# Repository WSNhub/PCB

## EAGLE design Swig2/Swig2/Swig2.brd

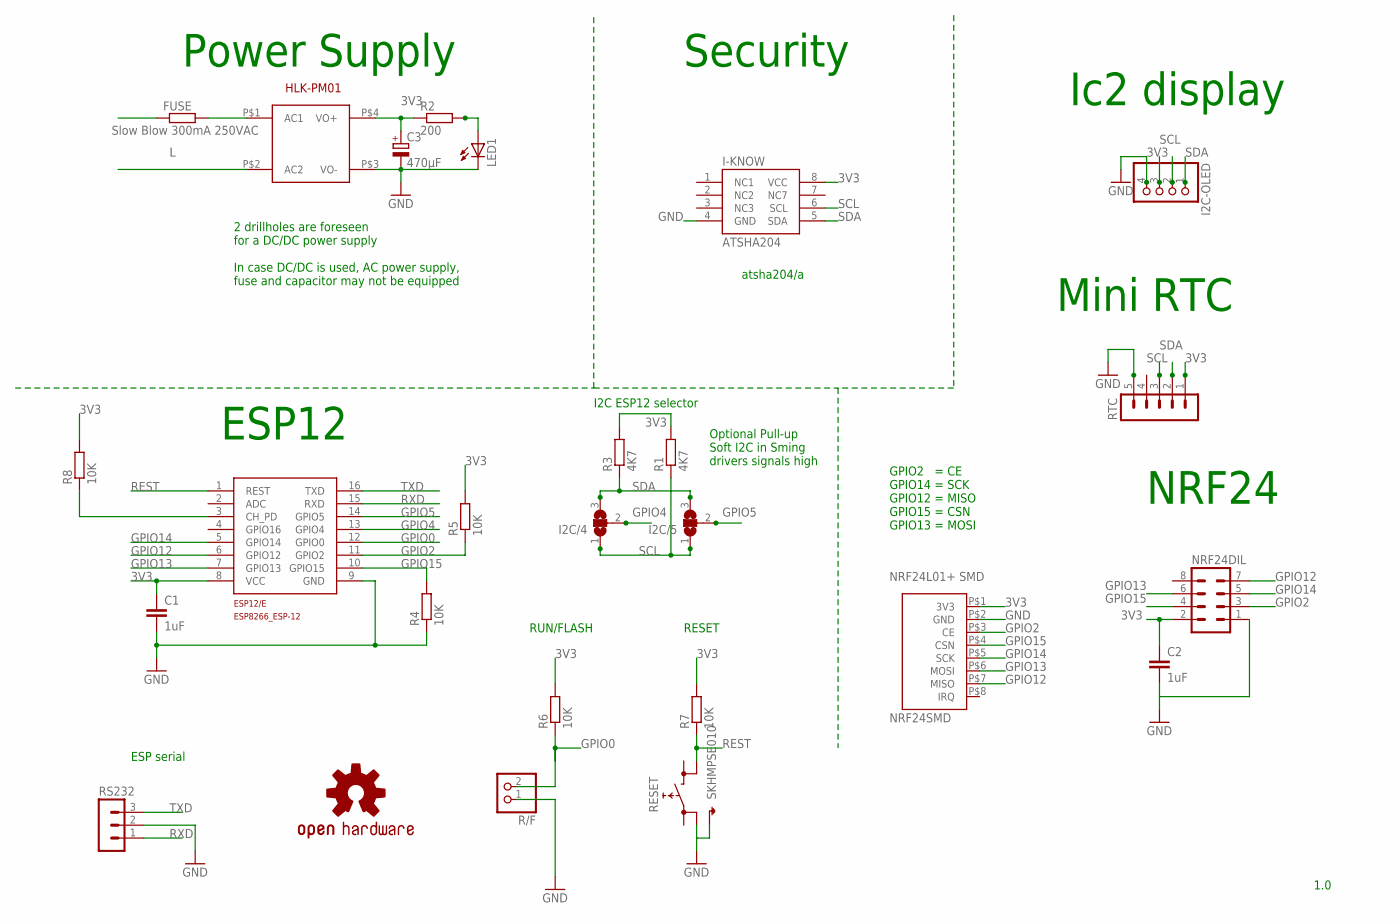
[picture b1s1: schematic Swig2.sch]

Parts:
C1, C2: 1uF; C0805
C3: 470µF; E5-8,5
ESP12/E: ESP8266-12GPIO04/05_CORRECTED; ESP8266-ESP12
FUSE: Slow Blow 300mA 250VAC; 0411V
HLK-PM01: HLK-PM01
I2C-OLED: PINHD-1X4; 1X04
I2C/4, I2C/5: SJ2W; SJ_2
I-KNOW: ATSHA204; SOIC8
LED1: LED5MM
LOGO2: OSHW-LOGOS; OSHW-LOGO-S
NRF24DIL: MA04-2
NRF24SMD: NRF24L01+SMD
R1, R3: 4K7; R0805
R2: 200; R0805
R4, R5, R6, R7, R8: 10K; R0805
R/F: PINHD-1X2; 1X02
RESET: SKHMPSE010; SKHMPXE010
RS232: MA03-1
RTC: MA05-1

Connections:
3V3: C1.1, C2.1, C3.+, ESP12/E.8 (VCC), HLK-PM01.P$4 (VO+), I2C-OLED.3, I-KNOW.8 (VCC), NRF24DIL.2, NRF24SMD.P$1 (3V3), R1.2, R2.1, R3.2, R5.2, R6.2, R7.2, R8.2, RTC.1
GND: C1.2, C2.2, C3.-, ESP12/E.9 (GND), HLK-PM01.P$3 (VO-), I2C-OLED.4, I-KNOW.4 (GND), LED1.K (C), NRF24DIL.1, NRF24SMD.P$2 (GND), R4.1, R/F.1, RESET.2 (1.2), RESET.5 (SH), RS232.2, RTC.5
GPIO0: ESP12/E.12 (GPIO0), R6.1, R/F.2
GPIO2: ESP12/E.11 (GPIO2), NRF24DIL.3, NRF24SMD.P$3 (CE), R5.1
GPIO4: ESP12/E.13 (GPIO4), I2C/4.2
GPIO5: ESP12/E.14 (GPIO5), I2C/5.2
GPIO12: ESP12/E.6 (GPIO12), NRF24DIL.7, NRF24SMD.P$7 (MISO)
GPIO13: ESP12/E.7 (GPIO13), NRF24DIL.6, NRF24SMD.P$6 (MOSI)
GPIO14: ESP12/E.5 (GPIO14), NRF24DIL.5, NRF24SMD.P$5 (SCK)
GPIO15: ESP12/E.10 (GPIO15), NRF24DIL.4, NRF24SMD.P$4 (CSN), R4.2
L: HLK-PM01.P$2 (AC2)
unnamed: FUSE.2, HLK-PM01.P$1 (AC1)
unnamed: ESP12/E.3 (CH_PD), R8.1
unnamed: LED1.A, R2.2
REST: ESP12/E.1 (REST), R7.1, RESET.4 (2.2)
RXD: ESP12/E.15 (RXD), RS232.1
SCL: I2C-OLED.2, I2C/4.1, I2C/5.1, I-KNOW.6 (SCL), R1.1, RTC.3
SDA: I2C-OLED.1, I2C/4.3, I2C/5.3, I-KNOW.5 (SDA), R3.1, RTC.2
TXD: ESP12/E.16 (TXD), RS232.3

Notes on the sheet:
ESP serial
RUN/FLASH
RESET
NRF24
1.0
I2C ESP12 selector
atsha204/a
Mini RTC
Power Supply
Security
ESP12
Optional Pull-up Soft I2C in Sming drivers signals high
2 drillholes are foreseen for a DC/DC power supply In case DC/DC is used, AC power supply, fuse and capacitor may not be equipped
Ic2 display
GPIO2 = CE GPIO14 = SCK GPIO12 = MISO GPIO15 = CSN GPIO13 = MOSI

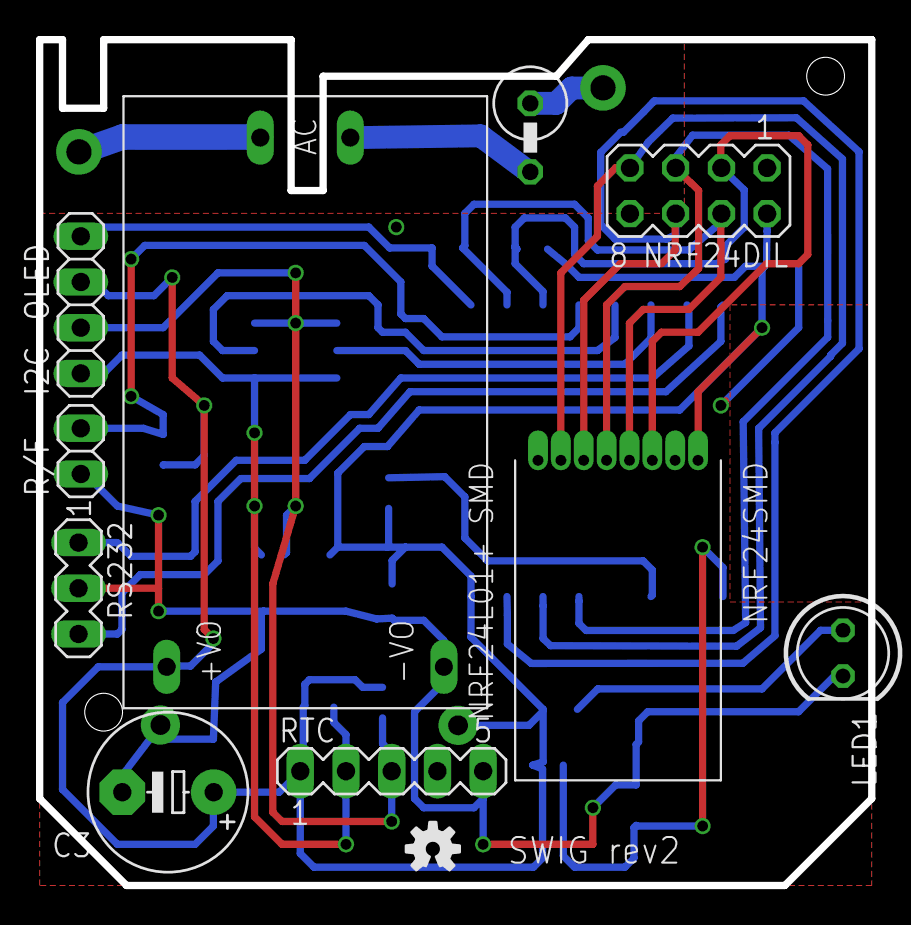
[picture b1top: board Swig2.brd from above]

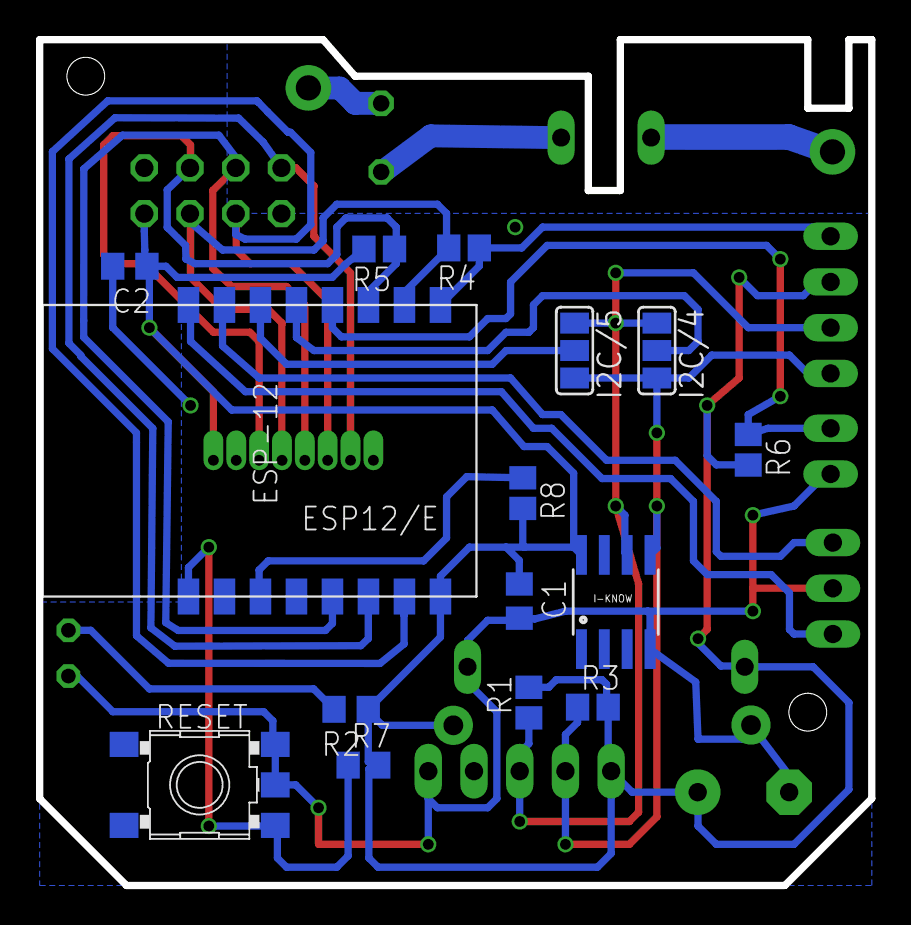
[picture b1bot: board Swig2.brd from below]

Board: 2 copper layers, 46.2 x 47.0 mm, 26 parts (15 on the bottom side), 18 nets.

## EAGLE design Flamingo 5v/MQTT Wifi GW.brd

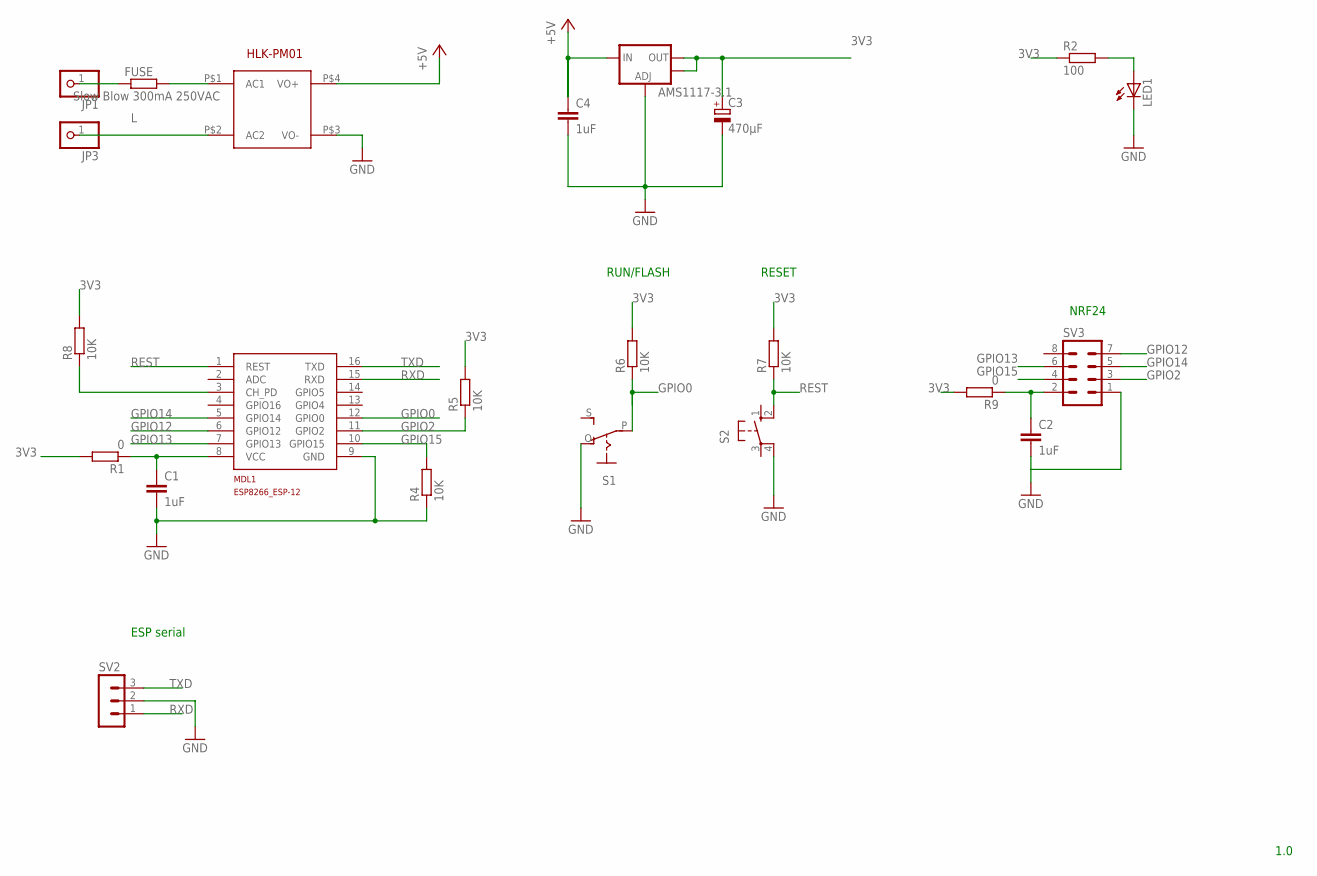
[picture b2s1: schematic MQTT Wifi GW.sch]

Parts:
AMS1117-3.1: V_REG_LM1117SOT223; SOT223
C1, C2, C4: 1uF; C1206K
C3: 470µF; E5-8,5
FUSE: Slow Blow 300mA 250VAC; 0411V
HLK-PM01: HLK-PM01
JP1, JP3: PINHD-1X1; 1X01
LED1: LED5MM
MDL1: ESP8266-12GPIO04/05_CORRECTED; ESP8266-ESP12
R1: 0; R0805
R2: 100; 0207/10
R4, R5, R6, R7: 10K; R0805
R8: 10K; R1206
R9: 0; R1206
S1: EG1218S; EG1218
S2: 10-XX; B3F-10XX
SV2: MA03-1
SV3: MA04-2

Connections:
3V3: AMS1117-3.1.2 (OUT), AMS1117-3.1.4 (OUT), C3.+, R1.2, R2.1, R5.2, R6.2, R7.2, R8.2, R9.2
+5V: AMS1117-3.1.3 (IN), C4.1, HLK-PM01.P$4 (VO+)
GND: AMS1117-3.1.1 (ADJ), C1.2, C2.2, C3.-, C4.2, HLK-PM01.P$3 (VO-), LED1.K (C), MDL1.9 (GND), R4.1, S1.O, S2.4 (P1), SV2.2, SV3.1
GPIO0: MDL1.12 (GPIO0), R6.1, S1.P
GPIO2: MDL1.11 (GPIO2), R5.1, SV3.3
GPIO12: MDL1.6 (GPIO12), SV3.7
GPIO13: MDL1.7 (GPIO13), SV3.6
GPIO14: MDL1.5 (GPIO14), SV3.5
GPIO15: MDL1.10 (GPIO15), R4.2, SV3.4
L: HLK-PM01.P$2 (AC2), JP3.1
unnamed: C2.1, R9.1, SV3.2
unnamed: C1.1, MDL1.8 (VCC), R1.1
unnamed: FUSE.1, JP1.1
unnamed: FUSE.2, HLK-PM01.P$1 (AC1)
unnamed: MDL1.3 (CH_PD), R8.1
unnamed: LED1.A, R2.2
REST: MDL1.1 (REST), R7.1, S2.2 (S1)
RXD: MDL1.15 (RXD), SV2.1
TXD: MDL1.16 (TXD), SV2.3

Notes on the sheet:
ESP serial
RUN/FLASH
RESET
NRF24
1.0

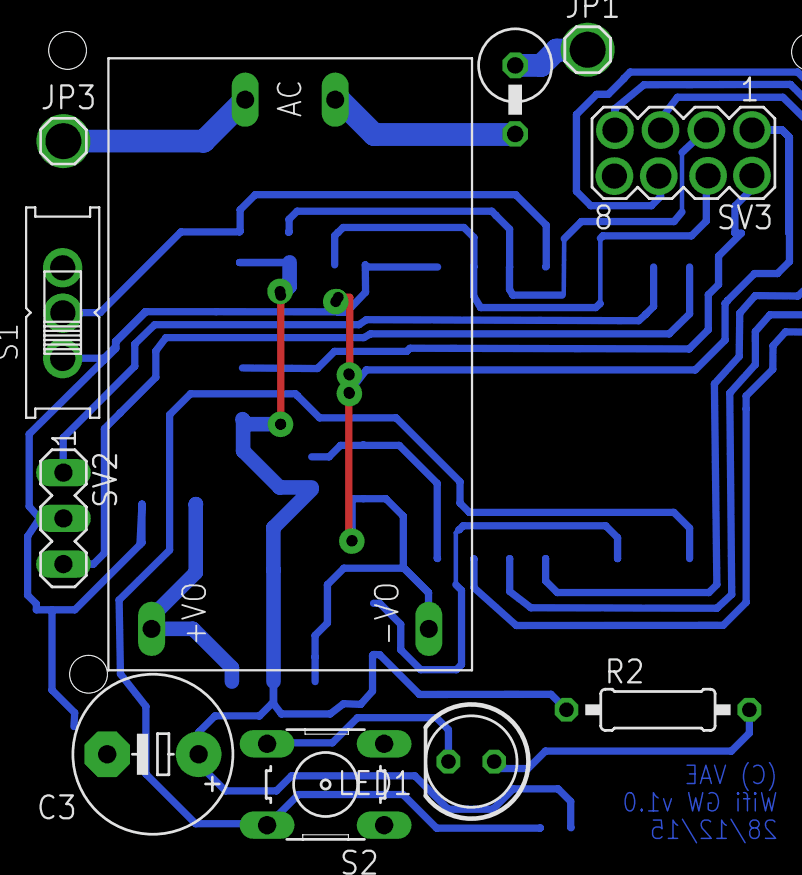
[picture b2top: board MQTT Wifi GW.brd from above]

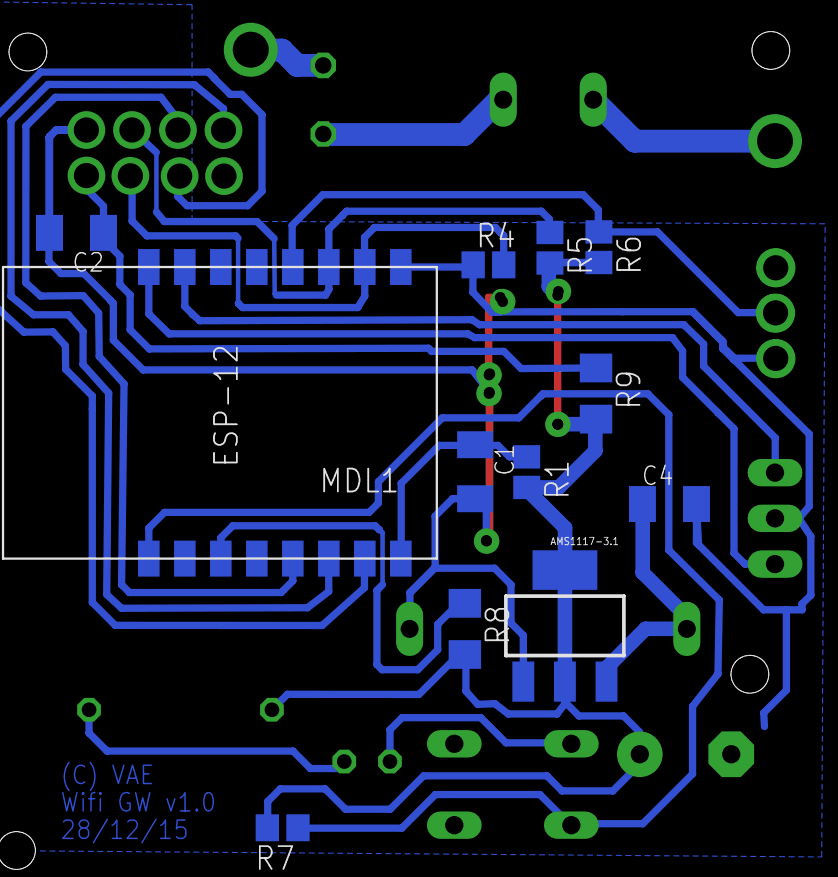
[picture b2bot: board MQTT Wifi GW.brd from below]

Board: 2 copper layers, 23 parts (12 on the bottom side), 19 nets.

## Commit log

2016-01-26 Initial version
2016-05-18 Swig2 info : PCB, BOM, link to assembly video
2016-05-18 update link info

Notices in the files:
parts and their libraries:
SparkFun-PowerIC: Licensing: Creative Commons ShareAlike 4.0 International - https://creativecommons.org/licenses/by-sa/4.0
SparkFun-Aesthetics: Licensing: CC v3.0 Share-Alike You are welcome to use this library for commercial purposes.
